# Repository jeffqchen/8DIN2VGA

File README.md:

# 8DIN2VGA

A dongle for console with 8 pin Mini DIN RGBs video output.

------

This adapter allows you to plug into consoles that outputs RGBs and audio via a 8 pin Mini DIN jack and transmit the signals through a VGA cable. This includes but not limited to:
- NESRGB modded NES/Famicom
- 3DORGB modded with 3DORGB and 8 pin Mini DIN option
- Certain supergun boards

 Audio can be sent within the VGA cable, or extracted from the 3.5mm jack on the dongle. Buzzing may be noticeable when audio is transmited through the VGA cable in certain scenes in certain games. This is due to insufficient shielding in most VGA cables. If you find the buzzing to be annoying, please use the 3.5mm jack on the dongle for audio output. This will ensure the cleanest possible audio.

-----------

## Different Designs

There are two types of 8 pin Mini DIN connectors you can purchase. One typically used for building cables, the other that's directly soldered to the PCB. Hence I've made two distinct designs for each of them. Comparatively speaking, the PCB-type design is easier to assemble. Otherwise, they function perfectly the same.

[Building Guide for Plug-Type 8DIN2VGA](./8DIN2VGA_Plug/README.md)

[Building Guide for PCB-Type 8DIN2VGA](./8DIN2VGA_PCB/README.md)

-----------

Shield: [![CC BY-SA 4.0][cc-by-sa-shield]][cc-by-sa]

This work is licensed under a
[Creative Commons Attribution-ShareAlike 4.0 International License][cc-by-sa].

[![CC BY-SA 4.0][cc-by-sa-image]][cc-by-sa]

[cc-by-sa]: http://creativecommons.org/licenses/by-sa/4.0/
[cc-by-sa-image]: https://licensebuttons.net/l/by-sa/4.0/88x31.png
[cc-by-sa-shield]: https://img.shields.io/badge/License-CC%20BY--SA%204.0-lightgrey.svg

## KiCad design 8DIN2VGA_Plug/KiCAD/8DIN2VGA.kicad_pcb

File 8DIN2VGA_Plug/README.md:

# 8DIN2VGA Plug-Type
-----------

## Parts

- PCB
  - [Main](https://oshpark.com/shared_projects/XZ4A1SB4)
  - [Top Sub **0.8mm thickness**](https://oshpark.com/shared_projects/FF7H08du)
  - [Bottom Sub **0.8mm thickness**](https://oshpark.com/shared_projects/HFqqnMif)

*Note the Top & Bottom sub boards MUST be ordered with the 0.8mm thickness option, otherwise they won't fit!*

- 8 pin Mini DIN Male (Plug Type) - [Link](https://github.com/jeffqchen/JeffParts/blob/main/Connectors/Mini%20DIN/8Pin/Cable/info.md)

- VGA Port Slim Female - [Link](https://github.com/jeffqchen/JeffParts/blob/main/Connectors/HD15/Slim/Female%20PCB/info.md)

- 3.5mm Headphone Jack - [Link](https://github.com/jeffqchen/JeffParts/blob/main/Connectors/3.5mm%20Audio%20Jack/Vertical%205-Pin%20PCB/info.md)

- M2x20mm screw and hex nut - [Link](https://github.com/jeffqchen/JeffParts/blob/main/Parts/M2%20M3%20Hex%20Screw%20%26%20Nut/info.md)

- 2x SMD Capacitor 10uF 6.3V 0603 size

-----------
## Print

Print the parts with the mating surface downwards, with support.

-----------
## Assembly

Soldering in this project is essential and somewhat challenging. This applies to soldering the sub boards to the pin header, as well as the landing pads on the main PCB. If you leave any gap, the assembly will not fit and the shells won't close properlly.

 First, put the 3 boards together in their final position, and fix the assembly with the help from reverse tweezers or clamps. Try and fit the 0.8mm PCBs in between the gaps between the back side of the 3 rows of pins. Push the sub PCBs all the way until they touch the pin header. Make sure the pins and their pads are aligned properlly.

 ----

 ## IMPORTANT

 *The plastic of the plug pin header is weak against heat and should not be heated for more than a few seconds in one go. Try to cool it down between soldering by blowing air on it.*

 ----

 Solder the two pins on the bottom side of the bottom PCB with proper amount of solder. Then release the clamping and remove the top and main PCB. Proceed to solder the center row of the pins to the bottom PCB.

 Again, put everything back together with clamping. Then, solder the top PCB to the top row of the pin header. Now, release the clamping and remove only the main PCB. The assembly should look as follows:

 Now, put the 2 pieces of metal shielding over the pin header part:

 Shove the assembly through the round hole on the inside shell, all the way in:

 Test fit the main PCB firmly into the shell and the plug and see if all the landing pads line up correctly:

 Now, take out the main PCB and solder on the 10uF SMD caps and the headphone jack:

 Again, insert the main PCB into its final position. Pinch the two sub boards into the main with a clapm or reverse tweezers. Make sure there's no gap between the sub and main PCB. Then, solder all the landing pads with proper amount of solder.

 Then, use ample amount of solder to attach the metal shield of the plug to the exposed copper area onto both sides of the main PCB。

 Last, solder in the VGA port. Soldering is done.

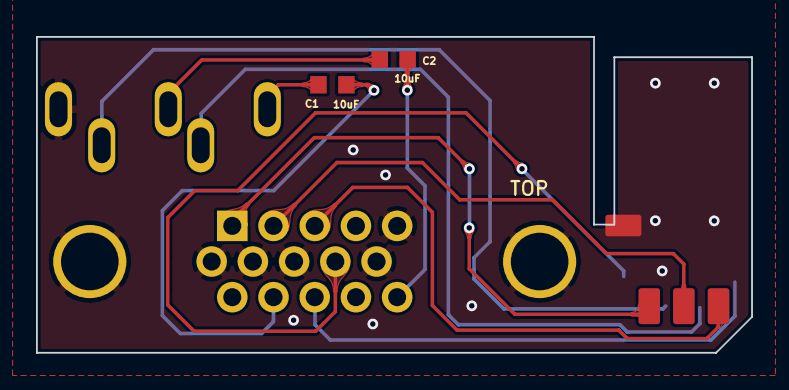
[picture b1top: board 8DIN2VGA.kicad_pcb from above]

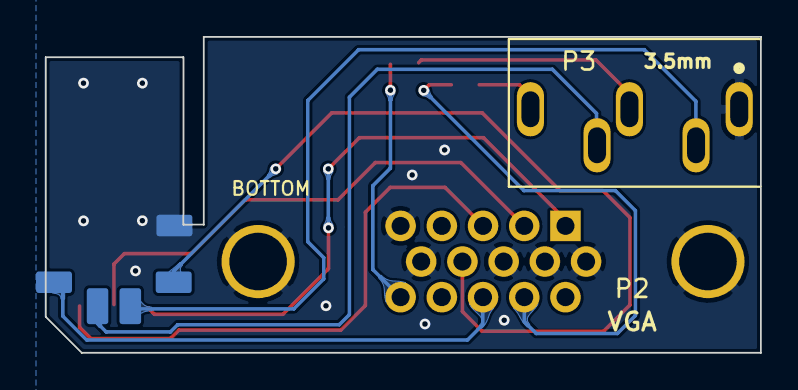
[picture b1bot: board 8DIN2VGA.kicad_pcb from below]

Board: 2 copper layers, 39.7 x 17.5 mm, 5 parts (2 on the bottom side), 12 nets.

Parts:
C1, C2: 10uF; CAP_SMD_0603
P1: 8_pin_DIN_Landing; 8DIN_Landing
P2: VGA; VGA_female_rightangle_slim
P3: 3.5mm_vertical

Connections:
/+5V: P1.5, P2.9
/Audio_L_VGA: C1.2, P2.12
/Audio_L_to_Jack: P1.2, P3.2
/Audio_L_to_VGA: C1.1, P3.4
/Audio_R_VGA: C2.1, P3.5
/Audio_R_to_Jack: P1.1, P3.3
/BLUE: P1.6, P2.3
/GREEN: P1.7, P2.2
/RED: P1.8, P2.1
/SYNC: P1.3, P2.13
GND: P1.4, P2.5, P2.6, P2.7, P2.8, P2.10, P2.S1, P2.S2, P3.1
unnamed: C2.2, P2.15

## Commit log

2021-09-27 Initial Upload
2021-09-27 More pics
2021-10-23 Update with new 5V design
2021-10-23 Update 3D printed shell
2021-11-15 Add Neo 8DIN2VGA & Reorganize Files
2021-11-15 Readme for neo 8din2vga
2022-03-22 Update guides with parts list
2022-03-23 Update VGA URL
2022-08-09 Change license type
